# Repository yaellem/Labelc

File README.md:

These are the embadded code done for the Lab Elec piscine.
Week 1: Assemble component on breadboard and develop code you will embade on you MCU
Week 2: Micro welding on PCB
Week 3: Electronic Schematics on Kicads and micro-welding

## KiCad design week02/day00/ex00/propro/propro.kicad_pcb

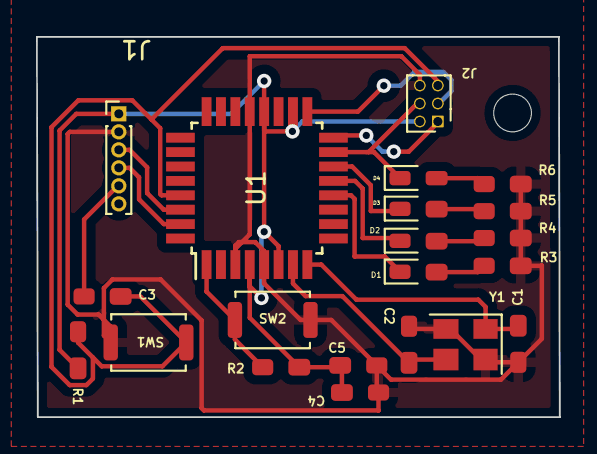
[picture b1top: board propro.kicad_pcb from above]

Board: 2 copper layers, 29.0 x 21.1 mm, 22 parts (0 on the bottom side), 19 nets.

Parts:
C1, C2: 22pF; Capacitor
C3, C4: 100nF; Capacitor
C5: 10uF; Capacitor
D1, D2, D3, D4: LED; Led
H1: MountingHole
J1: Conn_01x86; connector
J2: AVR-ISP; avr-isr
R1, R2: 10k; resistence
R3, R4, R5, R6: 330R; resistence
SW1, SW2: SW_PUSH; sw
U1: Atmega328p; atmega328pau
Y1: 16MHz

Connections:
+5V: C4.2, C5.2, J1.1, J2.2, R1.2, R2.2, U1.4 (VCC), U1.6 (VCC), U1.18 (AVCC), U1.20 (AREF)
/BUT_0: R2.1, SW2.1, U1.1 (PD3)
/LED_0: D1.1, U1.12 (PB0)
/LED_1: D2.1, U1.13 (PB1)
/LED_2: D3.1, U1.14 (PB2)
/LED_3_MOSI: D4.1, J2.4, U1.15 (PB3)
/MCU_RX: J1.3, U1.30 (PD0)
/MCU_TX: J1.4, U1.31 (PD1)
/MISO: J2.1, U1.16 (PB4)
/SCK: J2.3, U1.17 (PB5)
/~RESET: C3.2, J2.5, R1.1, SW1.1, U1.29 (~RESET/PC6)
GND: C1.1, C2.1, C4.1, C5.1, J1.2, J2.6, R3.2, R4.2, R5.2, R6.2, SW1.2, SW2.2, U1.3 (GND), U1.5 (GND), U1.21 (GND), Y1.2, Y1.4
unnamed: C1.2, U1.8 (XTAL2/PB7), Y1.1
unnamed: C2.2, U1.7 (XTAL1/PB6), Y1.3
unnamed: C3.1, J1.5
unnamed: D1.2, R3.1
unnamed: D2.2, R4.1
unnamed: D3.2, R5.1
unnamed: D4.2, R6.1

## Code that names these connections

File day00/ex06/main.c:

#include <avr/io.h>

int main()
{
	DDRB = 1 << PB0;
	DDRB |= 1 << PB1;
	DDRB |= 1 << PB2;
	DDRB |= 1 << PB3;
	DDRD = 0;
	PORTB = 0;
	uint8_t c = 0;
	for (;;)
	{
		if  ((PIND & (1 << PD3)) == 0)
		{
			c = c + 1;
			PORTB = c & 0xf;	
			for (uint32_t i = 0; i < 1000000; i++);
		}
	}
	return 0;
}

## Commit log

2022-01-10 Fix ex05 and ex06
2022-01-11 to finish ex01 day01
2022-01-12 done
2022-01-13 all finished
2022-01-15 f*ckin weirdies stuffs
2022-01-17 RUSH TO FINISH LATER, done day00 week01 NO BONUS
2022-01-18 RUSH TO FINISH LATER, done soudure, done day02
2022-01-19 RUSH TO FINISH LATER, done soudure, done day03
2022-01-29 add week02
2022-01-31 add pcd + footprint lib
